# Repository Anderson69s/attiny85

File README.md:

# attiny85

L’écosystème Arduino sert de passerelle USB <-> Serial <-> ISP.

Voici les instructions pour envoyer du code et fabriquer son programmateur à partir d’un Arduino UNO.

# MATÉRIEL NÉCESSAIRE

* 1 Arduino UNO
* 1 attiny85
* 1 câble USB type A
* 6 câbles de prototypages Femelle / Mâle

# INSTALLATION ARDUINO IDE

Rendez-vous sur le site   dans la section Software :

Télécharger la dernière version de l’IDE pour votre système d’exploitation :

Vous pouvez choisir de faire une donation ou non juste avant de lancer le téléchargement :

Installez l’Arduino IDE sur votre ordinateur. Pour les utilisateurs de Windows je vous recommande d’utiliser l’installeur qui contient le pilote USB pour les cartes Arduino.

# MISE EN PLACE DU PROGRAMMATEUR

Lancez l’Arduino IDE

Ouvrez ensuite l’exemple -> Arduino ISP :

Connectez ensuite juste votre Arduino UNO à votre ordinateur à l’aide du cordon USB et uploadez le code :

Lancer l'upload Upload Terminé
C’est terminé, votre Arduino UNO est prêt pour envoyer du code sur votre attiny85.

# DEFINITION DE CARTE

Rendez-vous dans les préférences de l’Arduino IDE :

Ajoutez l’adresse suivante :
```https://raw.githubusercontent.com/damellis/attiny/ide-1.6.x-boards-manager/package_damellis_attiny_index.json```

Validez en cliquant sur OK. Allez alors dans le gestionnaire de cartes :

Gestionnaire de Cartes, Ajout de "attiny"

**Une fois ces opérations faites, redémarrez l’Arduino IDE afin que tout soit bien pris en compte.**

Vous pouvez alors choisir les bons paramètres pour la carte :

# SOURCES & UPLOAD

Il ne reste plus qu’à connecter l’Arduino UNO avec la carte  :

ATTINY85  | Arduino Uno
------------ | -------------
+5V  | +5V
GND | GND
RESET | D10
PB0 | D11
PB1 | D12
PB2 | D13

Puis à envoyer le code sur l'attiny85 avec le bouton upload de l'Arduino IDE 🙂

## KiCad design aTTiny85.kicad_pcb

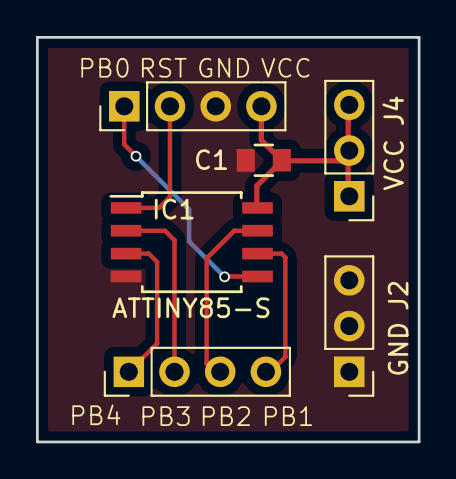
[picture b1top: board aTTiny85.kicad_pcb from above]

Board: 2 copper layers, 21.2 x 22.5 mm, 6 parts (0 on the bottom side), 8 nets.

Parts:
C1: 10uF; C_0805
IC1: ATTINY85-S; SOIJ-8_5.3x5.3mm_Pitch1.27mm
J1: Connecteur 1; Pin_Header_Straight_1x04_Pitch2.54mm
J2: GND; Pin_Header_Straight_1x03_Pitch2.54mm
J3: Connecteur 2; Pin_Header_Straight_1x04_Pitch2.54mm
J4: VCC; Pin_Header_Straight_1x03_Pitch2.54mm

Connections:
GND: C1.2, IC1.4, J2.1, J2.2, J2.3, J3.3
PB0: IC1.5, J3.1
PB1: IC1.6, J1.4
PB2: IC1.7, J1.3
PB3: IC1.2, J1.2
PB4: IC1.3, J1.1
RST: IC1.1, J3.2
VCC: C1.1, IC1.8, J3.4, J4.1, J4.2, J4.3

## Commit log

2017-12-09 Initial Release
